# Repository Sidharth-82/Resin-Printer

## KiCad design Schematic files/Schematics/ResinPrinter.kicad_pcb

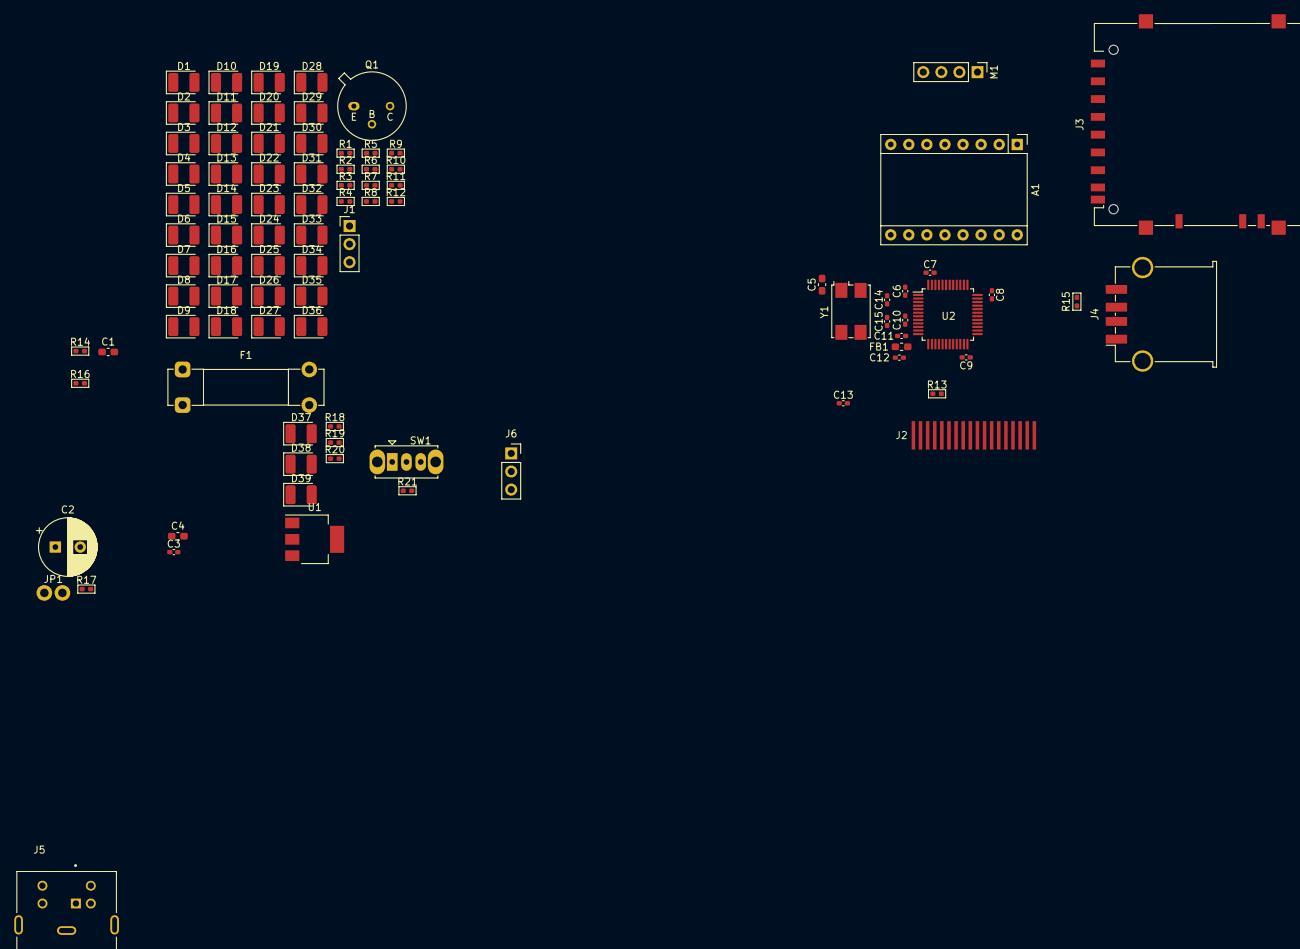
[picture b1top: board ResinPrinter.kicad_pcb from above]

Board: 2 copper layers, 91 parts (0 on the bottom side), 78 nets, no tracks yet.

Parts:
A1: A4988; Pololu_Breakout-16_15.2x20.3mm
C1: 100nC; C_0603_1608Metric_Pad1.08x0.95mm_HandSolder
C2: 100uC; CP_Radial_D8.0mm_P3.50mm
C3, C6, C7, C8, C9, C13: 100nC; C_0402_1005Metric_Pad0.74x0.62mm_HandSolder
C4, C5: 10uC; C_0603_1608Metric_Pad1.08x0.95mm_HandSolder
C10: 10nC; C_0402_1005Metric_Pad0.74x0.62mm_HandSolder
C11, C12: 1uC; C_0402_1005Metric_Pad0.74x0.62mm_HandSolder
C14, C15: 14pC; C_0402_1005Metric_Pad0.74x0.62mm_HandSolder
D1, D2, D3, D4, D5, D6, D7, D8, D9, D10, D11, D12, D13, D14, D15, D16, D17, D18, D19, D20, D21, D22, D23, D24, D25, D26, D27, D28, D29, D30, D31, D32, D33, D34, D35, D36: LED; LED_1210_3225Metric_Pad1.42x2.65mm_HandSolder
D37, D38, D39: RED; LED_1210_3225Metric_Pad1.42x2.65mm_HandSolder
F1: 500mA; Fuseholder_Clip-5x20mm_Bel_FC-203-22_Lateral_P17.80x5.00mm_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
FB1: 120R; L_0603_1608Metric_Pad1.05x0.95mm_HandSolder
J1: Conn_01x03_Pin; PinHeader_1x03_P2.54mm_Vertical
J2: 18Pin_LCD_Panel
J3: SD_Card; SD_Hirose_DM1AA_SF_PEJ82
J4: USB_A; USB_A_TE_292303-7_Horizontal
J5: Mini-DIN-5; CUI_MD-50SM
J6: UV LED Socket; PinSocket_1x03_P2.54mm_Vertical
JP1: Open; Jumper_P2.54mm_D1.2mm
M1: Z-Axis Stepper Motor; PinHeader_1x04_P2.54mm_Vertical
Q1: 2N2222; TO-5-3_EBC
R1, R2, R3, R4, R5, R6, R7, R8, R9, R10, R11, R12: 120R; R_0402_1005Metric_Pad0.72x0.64mm_HandSolder
R13, R14, R17, R21: 10kR; R_0402_1005Metric_Pad0.72x0.64mm_HandSolder
R15: 1.5kR; R_0402_1005Metric_Pad0.72x0.64mm_HandSolder
R16: 1kR; R_0402_1005Metric_Pad0.72x0.64mm_HandSolder
R18, R20: 150R; R_0402_1005Metric_Pad0.72x0.64mm_HandSolder
R19: 500R; R_0402_1005Metric_Pad0.72x0.64mm_HandSolder
SW1: SW_SPDT; SW_Slide_1P2T_CK_OS102011MS2Q
U1: LD1117S33TR_SOT223; SOT-223-3_TabPin2
U2: STM32F103C8Tx; LQFP-48_7x7mm_P0.5mm
Y1: 16MHz; Crystal_SMD_7050-4Pin_7.0x5.0mm

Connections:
+3V3: A1.2 (VDD), C1.1, C5.1, C6.1, C7.1, C8.1, C9.1, C12.1, F1.2, FB1.2, J2.9 (VDD), J3.4 (VDD), R13.1, R14.1, R15.1, SW1.3 (C), U2.1 (VBAT), U2.24 (VDD), U2.36 (VDD), U2.48 (VDD)
+5V: C3.1, D37.2 (A), J4.1 (VBUS), J5.3, J5.5, U1.3 (VI)
+12V: A1.8 (VMOT), C2.1, D38.2 (A), J1.1, J5.1, J6.1, Q1.1 (E)
/STM32F103C8T6_MCU/+3.3VA: C10.1, C11.1, FB1.1, U2.9 (VDDA)
/STM32F103C8T6_MCU/BOOT0_R22_P1: R21.1, U2.2 (PC13), U2.44 (BOOT0)
/STM32F103C8T6_MCU/HSE_IN_Y1_P1: C14.1, U2.5 (PD0), Y1.1
/STM32F103C8T6_MCU/HSE_OUT_Y1_P3: C15.1, U2.6 (PD1), Y1.3
/STM32F103C8T6_MCU/NRST_C17_P1: C13.1, U2.7 (NRST)
/STM32F103C8T6_MCU/PB7_UV_LED_ON: J6.2, U2.43 (PB7)
/STM32F103C8T6_MCU/SW1_R22_P2: R21.2, SW1.2 (B)
/UVLED_Panel/PB7_UV_LED_ON: J1.2, Q1.2 (B)
/UVLED_Panel/Q1_P3: D3.2 (A), D6.2 (A), D9.2 (A), D12.2 (A), D15.2 (A), D18.2 (A), D21.2 (A), D24.2 (A), D27.2 (A), D30.2 (A), D33.2 (A), D36.2 (A), Q1.3 (C)
GND: A1.1 (GND), A1.7 (GND), C1.2, C2.2, C3.2, C4.2, C5.2, C6.2, C7.2, C8.2, C9.2, C10.2, C11.2, C12.2, C13.2, C14.2, C15.2, J1.3, J2.1 (GND), J2.8 (GND), J3.3 (VSS), J3.6 (VSS), J4.4 (GND), J5.2, J5.4, J6.3, R1.1, R2.1, R3.1, R4.1, R5.1, R6.1, R7.1, R8.1, R9.1, R10.1, R11.1, R12.1, R17.2, R18.2, R19.1, R20.1, SW1.1 (A), U1.1 (GND), U2.8 (VSSA), U2.23 (VSS), U2.35 (VSS), U2.47 (VSS), Y1.2, Y1.4
unnamed: A1.4 (1A), M1.1
unnamed: A1.3 (1B), M1.2 (-)
unnamed: A1.5 (2A), M1.3
unnamed: A1.6 (2B), M1.4
unnamed: A1.13 (~RESET), JP1.2 (B)
unnamed: A1.14 (~SLEEP), JP1.1 (A)
unnamed: D1.2 (A), D2.1 (K)
unnamed: D1.1 (K), R1.2
unnamed: D2.2 (A), D3.1 (K)
unnamed: D4.2 (A), D5.1 (K)
unnamed: D4.1 (K), R2.2
unnamed: D5.2 (A), D6.1 (K)
unnamed: D7.2 (A), D8.1 (K)
unnamed: D7.1 (K), R3.2
unnamed: D8.2 (A), D9.1 (K)
unnamed: D10.2 (A), D11.1 (K)
unnamed: D10.1 (K), R4.2
unnamed: D11.2 (A), D12.1 (K)
unnamed: D13.2 (A), D14.1 (K)
unnamed: D13.1 (K), R5.2
unnamed: D14.2 (A), D15.1 (K)
unnamed: D16.2 (A), D17.1 (K)
unnamed: D16.1 (K), R6.2
unnamed: D17.2 (A), D18.1 (K)
unnamed: D19.2 (A), D20.1 (K)
unnamed: D19.1 (K), R7.2
unnamed: D20.2 (A), D21.1 (K)
unnamed: D22.2 (A), D23.1 (K)
unnamed: D22.1 (K), R8.2
unnamed: D23.2 (A), D24.1 (K)
unnamed: D25.2 (A), D26.1 (K)
unnamed: D25.1 (K), R9.2
unnamed: D26.2 (A), D27.1 (K)
unnamed: D28.2 (A), D29.1 (K)
unnamed: D28.1 (K), R10.2
unnamed: D29.2 (A), D30.1 (K)
unnamed: D31.2 (A), D32.1 (K)
unnamed: D31.1 (K), R11.2
unnamed: D32.2 (A), D33.1 (K)
unnamed: D34.2 (A), D35.1 (K)
unnamed: D34.1 (K), R12.2
unnamed: D35.2 (A), D36.1 (K)
unnamed: D37.1 (K), R18.1
unnamed: D38.1 (K), R19.2
unnamed: C4.1, D39.2 (A), F1.1, U1.2 (VO)
unnamed: D39.1 (K), R20.2
unnamed: J3.5 (CLK), R16.2
PA14_A4988_DIR: A1.16 (DIR), U2.37 (PA14)
PA15_A4988_STEP: A1.15 (STEP), U2.38 (PA15)
PB3_A4988_MS3: A1.12 (MS3), U2.39 (PB3)
PB4_A4988_MS2: A1.11 (MS2), U2.40 (PB4)
PB5_A4988_MS1: A1.10 (MS1), U2.41 (PB5)
PB6_A4988_ENABLE: A1.9 (~ENABLE), R17.1, U2.42 (PB6)
SD_CS: J3.1 (CD/DAT3), R14.2, U2.25 (PB12)
SPI_1_MISO: J2.7 (SDO), U2.16 (PA6)
SPI_1_MOSI: J2.6 (SDA), U2.17 (PA7)
SPI_1_SCLK: J2.3 (SCL), U2.15 (PA5)
SPI_2_MISO: J3.7 (DAT0), U2.27 (PB14)
SPI_2_MOSI: J3.2 (CMD), U2.28 (PB15)
SPI_2_SCLK: R16.1, U2.26 (PB13)
TFT_CS: J2.5 (CS), R13.2, U2.14 (PA4)
TFT_RS: J2.4 (RS), U2.13 (PA3)
TFT_RST: J2.2 (RESET), U2.12 (PA2)
USB_D+: J4.3 (D+), R15.2, U2.33 (PA12)
USB_D-: J4.2 (D-), U2.32 (PA11)

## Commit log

2024-02-27 stm32cube & schematic
2024-02-27 Finished Schematic
2024-02-27 footprints selected
